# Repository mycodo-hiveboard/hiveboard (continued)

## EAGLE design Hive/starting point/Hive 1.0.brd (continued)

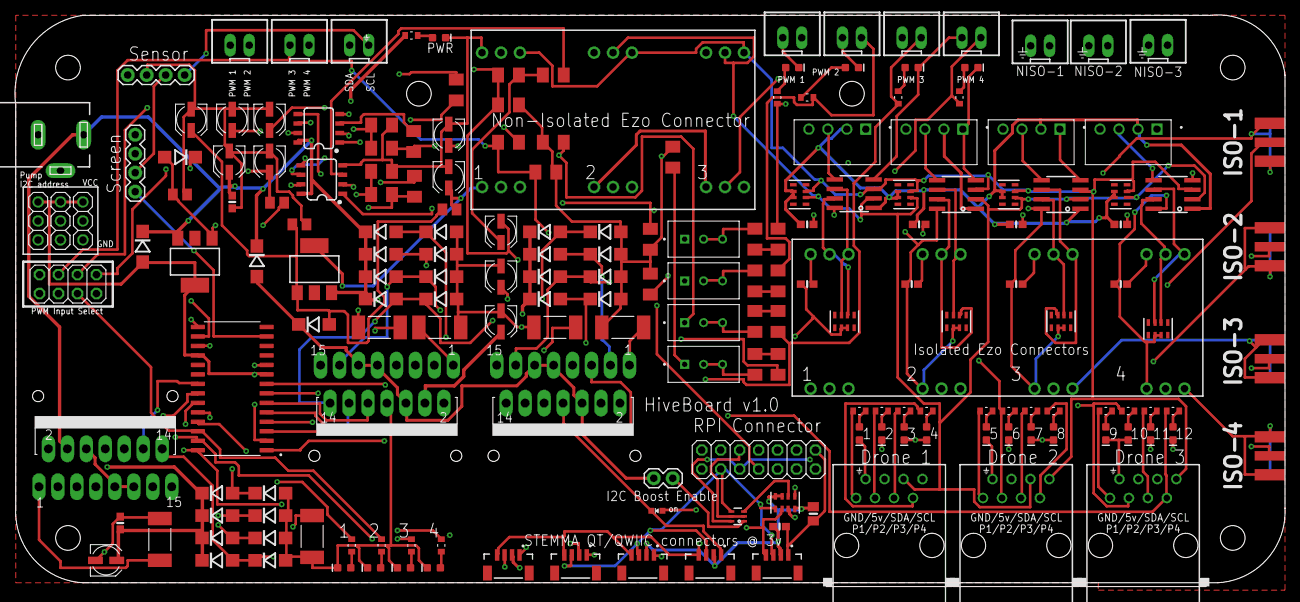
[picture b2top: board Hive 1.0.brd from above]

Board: 4 copper layers, 170.1 x 76.6 mm, 209 parts (0 on the bottom side), 127 nets.

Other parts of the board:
U$1, U$2: STAND-OFF

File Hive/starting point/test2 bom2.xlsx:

ID | Name | Designator | Footprint | Quantity | Manufacturer Part | Manufacturer | Supplier | Supplier Part | Price
1 | 100nF | C1,C2,C3 | C1206 | 3
2 | 1N4004 | D1,D10,D11,D12,D13,D14,D15,D16,D17,D18,D19,D2,D20,D21,D22,D23,D24,D3,D4,D5,D6,D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 | DO214BA | 26
3 | MOUNT-HOLE3.0 | H1,H2,H3,H4 | 3,0 | 4
4 | L298 | IC1,IC2,IC3 | MULTIWATT-15 | 3
5 | 0,5 x 2W | R1,R2,R3,R4,R5,R6 | R2512 | 6 | C469426
6 | RJ45-6L-B | PUMPBOX-1,PUMPBOX-3,PUMPBOX-2 | RJ45-NO-SHIELD | 3
7 | 1uf 50v | C1A1,C1B1,C1A2,C1B2 | C1206 | 4
8 | 100kΩ | R1A1,R1B1,R2A1,R2B1,R1A2,R1B2,R2A2,R2B2 | M1206 | 8
9 | 10kΩ | R5A1,R5B1,R5A2,R5B2 | M1206 | 4
10 | 75kΩ | R4A1,R4B1,R4A2,R4B2 | M1206 | 4
11 | 3296W-1-103 | R3-1A1,R3-1B1,R3-1A2,R3-1B2 | TRIM_3296W-1-103 | 4
12 | 180KΩ | R3-2A1,R3-2B1,R3-2A2,R3-2B2 | M1206 | 4
13 | 15kΩ | R3-3A1,R3-3B1,R3-3A2,R3-3B2 | M1206 | 4
14 | LM358 | U2,U1 | DIP08 | 2
15 | rr | X11 | JST-XH-02-PACKAGE-LONG-PAD | 1
16 | EZO2 | X12 | JST-XH-02-PACKAGE-LONG-PAD | 1
17 | PWM2 | (0-10V)-1 | JST-XH-02-PACKAGE-LONG-PAD | 1
18 | PWM1 | X4 | JST-XH-02-PACKAGE-LONG-PAD | 1
19 | PWM-IN | X5,X8 | JST-XH-02-PACKAGE-LONG-PAD | 2
20 | Sensor | X6 | JST-XH-04-PACKAGE-LONG-PAD | 1
21 | Screen Connector | X7 | JST-XH-04-PACKAGE-LONG-PAD | 1 | C225501
22 | 0.1uF | C6,C7,C4,C5,C8,C9,C10,C11,C15,C18 | 0603-NO | 10
23 | ISO154X | X13,X14,X16,X18 | SOIC8_150MIL | 4
24 | 10K | R9,R10,R7,R8,R11,R12,R13,R14 | RESPACK_4X0603 | 8
25 | RFM-0505S | PS1,PS2,PS3,PS4 | CONV_RFM-0505S | 4
26 | NISO-3 | X20 | JST-XH-02-PACKAGE-LONG-PAD | 1
27 | DATA | X21 | JST-XH-02-PACKAGE-LONG-PAD | 1
28 | 1X03-CLEANBIG | JP1,JP2,JP3,JP4,JP5,JP6,JP7,JP8,JP9,JP10,JP11,JP12,JP13,JP14 | 1X03-CLEANBIG | 14
29 | LM317MBSTT3 | IC4,IC5 | SOT223 | 2
30 | 240Ω | R15,R17 | M0805 | 2
31 | 1uF | C13,C16 | 085CS_1AR | 2 | C3348
32 | 10uF | C14,C17 | 085CS_1AR | 2 | C72485
33 | 394Ω | R16 | M0805 | 1
34 | 1X03 | SJ1,SJ2,SJ3 | 1X03 | 3
35 | 1N4002 | D33,D34 | DO214BA | 2
36 | 720Ω | R18 | M0805 | 1
37 | ISO-1 | ISO-1 | J502-ND-142-0701-801/806 | 1
38 | SMA-142-0701-801/806 | ISO-2,ISO-3,ISO-4 | J502-ND-142-0701-801/806 | 3
39 | CHIP-LED0603 | LED1,LED2,LED4,LED5,LED6,LED7,LED8,LED9,LED10,LED11,LED12,LED13,LED14,LED15,LED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 | CHIP-LED0603 | 25
40 | SDA | SDA | RESC1608X60N | 1
41 | 330R | SCL,12V,5V,3.3V,R20,R21,R22,R23,R24,R25,R26,R27,R28,R29,R30,R31,R32,R34,R33,R36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 | RESC1608X60N | 24
42 | MCP23017-E/SO | U3 | SOIC127P1030X265-28N | 1
43 | PWM4 | (0-10V)-2 | JST-XH-02-PACKAGE-LONG-PAD | 1
44 | PWM3 | X3 | JST-XH-02-PACKAGE-LONG-PAD | 1
45 | 2X04 | JP19 | 2X04 | 1
46 | 2X07 | JP15 | 2X07 | 1
47 | DCJ0202 | J1 | DCJ0202 | 1

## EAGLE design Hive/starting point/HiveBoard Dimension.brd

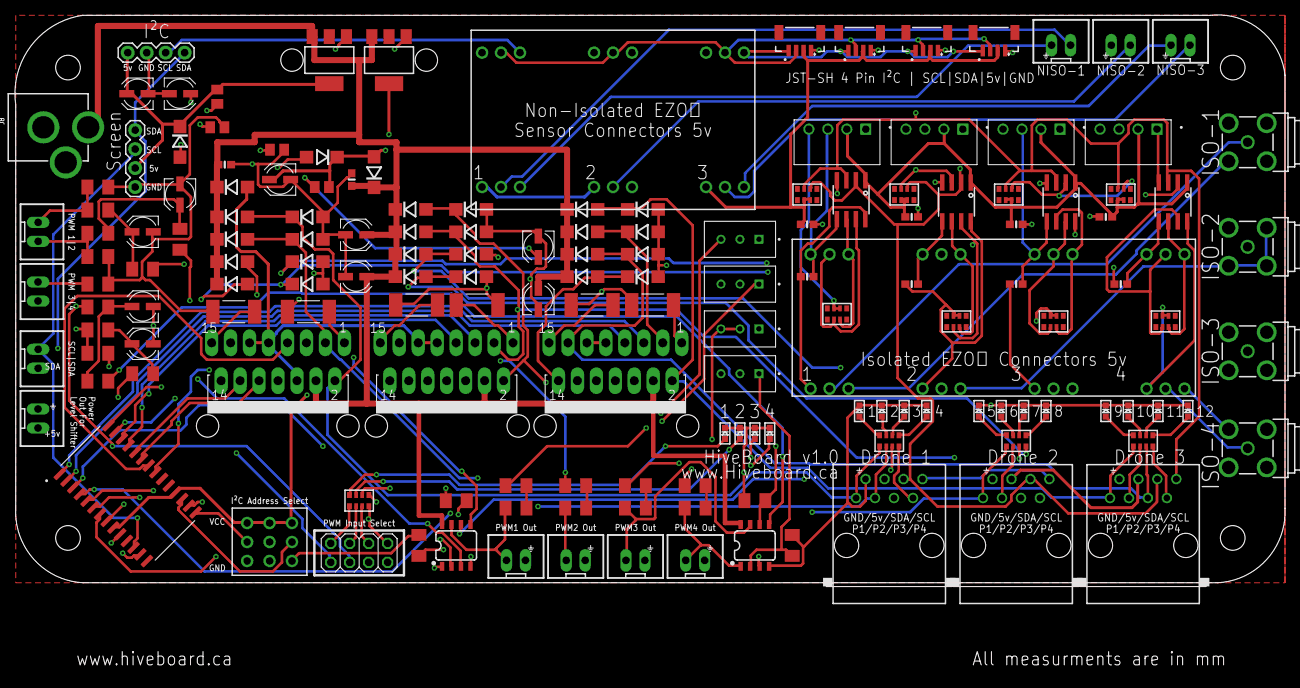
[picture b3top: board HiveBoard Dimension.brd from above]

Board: 4 copper layers, 170.1 x 76.6 mm, 178 parts (0 on the bottom side), 119 nets.

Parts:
C1, C7, C9: 100nF; UD-4X5,8_NICHICON
C1A1, C1A2, C1B1, C1B2, C5: 1uf 50v; UD-4X5,8_NICHICON
C2, C6, C10, C11, C12, C13, C14, C15, C16, C17: 0.1uF; 0603-NO
C3: 1uF 50v; UD-4X5,8_NICHICON
C4, C8: 10uF 35v; UD-4X5,8_NICHICON
D1, D2: 1N4002; DO214BA
D3, D4, D5, D6, D7, D8, D9, D10, D11, D12, D13, D14, D15, D16, D17, D18, D19, D20, D21, D22, D23, D24, D25, D26, D27, D28: 1N4004; DO214BA
H1, H2, H3, H4: STAND-OFF
IC1, IC3: LM317MBSTT3; SOT223
IC2, IC4, IC5: L298; MULTIWATT-15
J1, J5, J6, J7: Vertical Qwiic Connector; JST04_1MM_VERT
J2, J3: C2886705; 1X04
J8: POWER_JACK; POWER_JACK_PTH
JP1, JP2, JP3: 1X03_ROUND
JP4: 2X04
JP5, JP6, JP7, JP8, JP9, JP10, JP12, JP13, JP14, JP15, JP16, JP17, JP18, JP19: C2886705; 1X03-CLEANBIG
LED1, LED2, LED3, LED4, LED5, LED6, LED7, LED8, LED9, LED10, LED11, LED12, LED13, LED14, LED15, LED16: CHIPLED_0603
PS1, PS2, PS3, PS4: RFM-0505S; CONV_RFM-0505S
R1, R6, R8, R9, R10, R11: 0,5 x 2W; R2512
R1A1, R1A2, R1B1, R1B2, R2A1, R2A2, R2B1, R2B2: 100kΩ; M1206
R2, R3: 240Ω; M0805
R3-1A1, R3-1A2, R3-1B1, R3-1B2: 3296W-1-103; TRIM_3296W-1-103
R3-2A1, R3-2A2, R3-2B1, R3-2B2: 180KΩ; M1206
R3-3A1, R3-3A2, R3-3B1, R3-3B2: 15kΩ; M1206
R4: 720Ω; M0805
R4A1, R4A2, R4B1, R4B2: 75kΩ; M1206
R5: 394Ω; M0805
R5A1, R5A2, R5B1, R5B2: 10kΩ; M1206
R7, R15, R19, R22: 10kΩ; RESPACK_4X0603
R12, R13, R14, R16, R17, R18, R20, R21: 10KΩ; RESPACK_4X0603
U1: MCP23017-E/SO; SOIC127P1030X265-28N
U2, U3: LM358; SO08
X1, X2: PWM-IN; JST-XH-02-PACKAGE-LONG-PAD
X3, X11, X14, X17, X22: jst-xh-2; JST-XH-02-PACKAGE-LONG-PAD
X4: PWM1; JST-XH-02-PACKAGE-LONG-PAD
X5, X7: PWM2; JST-XH-02-PACKAGE-LONG-PAD
X6: PWM3; JST-XH-02-PACKAGE-LONG-PAD
X8, X10, X12, X15: ISO154X; SOIC8_150MIL
X9, X13, X16: RJ45-6L-B; RJ45-NO-SHIELD
X18, X19, X20, X21: BU-SMA-G

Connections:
+3.3V: C5.+, D11.C, D12.A, IC3.4, JP1.3, JP2.3, JP3.3, R3.2, U1.9, U1.18
+5V: C3.+, C10.1, C12.1, C14.1, C16.1, D1.C, D2.A, IC1.4, IC2.6, IC2.9, IC2.11, IC4.6, IC4.9, IC4.11, IC5.6, IC5.9, IC5.11, J1.3, J2.1, J3.2, J5.3, J6.3, J7.3, JP6.1, JP8.1, JP10.1, PS1.2, PS2.2, PS3.2, PS4.2, R2.2, R12.6, R12.7, R13.6, R13.7, R17.6, R17.7, R20.6, R20.7, X8.1, X9.4, X10.1, X12.1, X13.4, X15.1, X16.4, X22.2
+12V: C1.+, C2.2, C6.2, C7.+, C9.+, D2.C, D3.C, D5.C, D7.C, D9.C, D12.C, D13.C, D14.C, D15.C, D16.C, D21.C, D23.C, D25.C, D27.C, IC1.3, IC2.4, IC3.3, IC4.4, IC5.4, J8.PWR, U2.8, U3.8
GND: C1.-, C1A1.-, C1A2.-, C1B1.-, C1B2.-, C2.1, C3.-, C4.-, C5.-, C6.1, C7.-, C8.-, C9.-, C10.2, C12.2, C14.2, C16.2, D4.A, D6.A, D8.A, D10.A, D17.A, D18.A, D19.A, D20.A, D22.A, D24.A, D26.A, D28.A, IC2.8, IC4.8, IC5.8, J1.4, J2.2, J3.1, J5.4, J6.4, J7.4, J8.GND, J8.GNDBREAK, JP1.1, JP2.1, JP3.1, JP5.3, JP7.3, JP9.3, LED1.C, LED2.C, LED3.C, LED4.C, LED5.C, LED6.C, LED7.C, LED8.C, LED9.C, LED10.C, LED11.C, LED12.C, LED13.C, LED14.C, LED15.C, LED16.C, PS1.1, PS2.1, PS3.1, PS4.1, R1.1, R2A1.1, R2A2.1, R2B1.2, R2B2.2, R4.1, R5.1, R5A1.2, R5A2.2, R5B1.2, R5B2.2, R6.1, R8.1, R9.1, R10.1, R11.1, U1.10, U2.4, U3.4, X4.2, X5.2, X6.2, X7.2, X8.4, X9.2, X10.4, X12.4, X13.2, X15.4, X16.2, X22.1
IN-PUMP-1: IC2.5, U1.21
IN-PUMP-2: IC2.7, U1.22
IN-PUMP-3: IC2.10, U1.23
IN-PUMP-4: IC2.12, U1.24
IN-PUMP-5: IC4.5, U1.25
IN-PUMP-6: IC4.7, U1.26
IN-PUMP-7: IC4.10, U1.27
IN-PUMP-8: IC4.12, U1.28
IN-PUMP-9: IC5.5, U1.1
IN-PUMP-10: IC5.7, U1.2
IN-PUMP-11: IC5.10, U1.3
IN-PUMP-12: IC5.12, U1.4
IN-PWM-1: JP4.7, R1A1.2, R5A1.1, X1.1
IN-PWM-2: JP4.5, R1B1.1, R5B1.1, X1.2
IN-PWM-3: JP4.3, R1A2.2, R5A2.1, X2.1
IN-PWM-4: JP4.1, R1B2.1, R5B2.1, X2.2
ISO-1-5V: C11.1, JP13.1, PS1.4, R14.6, R14.7, X8.8
ISO-2-5V: C13.1, JP15.1, PS2.4, R16.6, R16.7, X10.8
ISO-3-5V: C15.1, JP17.1, PS3.4, R18.6, R18.7, X12.8
ISO-4-5V: C17.1, JP19.1, PS4.4, R21.6, R21.7, X15.8
ISO-GND-1: C11.2, JP12.3, PS1.3, X8.5
ISO-GND-2: C13.2, JP14.3, PS2.3, X10.5
ISO-GND-3: C15.2, JP16.3, PS3.3, X12.5
ISO-GND-4: C17.2, JP18.3, PS4.3, X15.5
ISO-PRB-1+: JP13.2, X18.1
ISO-PRB-1GND: JP13.3, X18.2, X18.3, X18.4, X18.5
ISO-PRB-2+: JP15.2, X19.1
ISO-PRB-2GND: JP15.3, X19.2, X19.3, X19.4, X19.5
ISO-PRB-3+: JP17.2, X20.1
ISO-PRB-3GND: JP17.3, X20.2, X20.3, X20.4, X20.5
ISO-PRB-4+: JP19.2, X21.1
ISO-PRB-4GND: JP19.3, X21.2, X21.3, X21.4, X21.5
LED1: JP4.2, R7.1, U1.5
LED2: JP4.4, R7.2, U1.6
LED3: JP4.6, R7.3, U1.7
LED4: JP4.8, R7.4, U1.8
unnamed: IC4.1, R9.2
unnamed: IC4.15, R8.2
unnamed: IC5.1, R11.2
unnamed: IC5.15, R10.2
unnamed: C8.+, D11.A, IC3.1, R3.1, R5.2
unnamed: R2A1.2, R3-1A1.1, U2.6
unnamed: LED1.A, R7.8
unnamed: R2B1.1, R3-1B1.1, U2.2
unnamed: IC2.1, R1.2
unnamed: IC2.15, R6.2
unnamed: C4.+, D1.A, IC1.1, R2.1, R4.2
unnamed: LED2.A, R7.7
unnamed: R3-1B1.2, R3-1B1.3, R3-2B1.1
unnamed: R3-2B1.2, R3-3B1.1
unnamed: R3-1A1.2, R3-1A1.3, R3-2A1.1
unnamed: R3-2A1.2, R3-3A1.1
unnamed: C1A1.+, R1A1.1, R4A2.1
unnamed: C1B1.+, R1B1.2, R4B1.1
unnamed: LED13.A, R22.8
unnamed: LED14.A, R22.7
unnamed: R4A2.2, U2.5
unnamed: R4B1.2, U2.3
unnamed: R3-1B2.2, R3-1B2.3, R3-2B2.1
unnamed: LED15.A, R22.6
unnamed: LED16.A, R22.5
unnamed: LED8.A, R15.5
unnamed: LED7.A, R15.6
unnamed: LED6.A, R15.7
unnamed: LED5.A, R15.8
unnamed: LED9.A, R19.8
unnamed: LED10.A, R19.7
unnamed: LED11.A, R19.6
unnamed: LED12.A, R19.5
unnamed: LED3.A, R7.6
unnamed: LED4.A, R7.5
unnamed: R3-2B2.2, R3-3B2.1
unnamed: R3-1A2.2, R3-1A2.3, R3-2A2.1
unnamed: R3-2A2.2, R3-3A2.1
unnamed: C1A2.+, R1A2.1, R4A1.1
unnamed: C1B2.+, R1B2.2, R4B2.1
unnamed: R2A2.2, R3-1A2.1, U3.6
unnamed: R2B2.1, R3-1B2.1, U3.2
unnamed: R4A1.2, U3.5
unnamed: R4B2.2, U3.3
unnamed: JP1.2, U1.15
unnamed: JP2.2, U1.16
unnamed: JP3.2, U1.17
NISO-PRB-1+: JP6.2, X11.2
NISO-PRB-1GND: JP6.3, X11.1
NISO-PRB-2+: JP8.2, X14.2
NISO-PRB-2GND: JP8.3, X14.1
NISO-PRB-3+: JP10.2, X17.2
NISO-PRB-3GND: JP10.3, X17.1
OUT-PUMP-1: D3.A, D4.C, IC2.2, R15.1, X9.1
OUT-PUMP-2: D5.A, D6.C, IC2.3, R15.2, X9.3
OUT-PUMP-3: D7.A, D8.C, IC2.13, R15.3, X9.5
OUT-PUMP-4: D9.A, D10.C, IC2.14, R15.4, X9.7
OUT-PUMP-5: D13.A, D17.C, IC4.2, R19.1, X13.1
OUT-PUMP-6: D14.A, D18.C, IC4.3, R19.2, X13.3
OUT-PUMP-7: D15.A, D19.C, IC4.13, R19.3, X13.5
OUT-PUMP-8: D16.A, D20.C, IC4.14, R19.4, X13.7
OUT-PUMP-9: D21.A, D22.C, IC5.2, R22.1, X16.1
OUT-PUMP-10: D23.A, D24.C, IC5.3, R22.2, X16.3
OUT-PUMP-11: D25.A, D26.C, IC5.13, R22.3, X16.5
OUT-PUMP-12: D27.A, D28.C, IC5.14, R22.4, X16.7
PWM-OUT-1: R3-3A1.2, U2.7, X4.1
PWM-OUT-2: R3-3B1.2, U2.1, X5.1
PWM-OUT-3: R3-3A2.2, U3.7, X6.1
PWM-OUT-4: R3-3B2.2, U3.1, X7.1
SCL: J1.1, J2.3, J3.3, J5.1, J6.1, J7.1, JP5.1, JP7.1, JP9.1, R12.3, R13.3, R17.3, R20.3, U1.12, X3.1, X8.3, X9.8, X10.3, X12.3, X13.8, X15.3, X16.8
SCL2: JP12.1, R14.3, X8.6
SCL3: JP14.1, R16.3, X10.6
SCL4: JP16.1, R18.3, X12.6
SCL5: JP18.1, R21.3, X15.6
SDA: J1.2, J2.4, J3.4, J5.2, J6.2, J7.2, JP5.2, JP7.2, JP9.2, R12.2, R13.2, R17.2, R20.2, U1.13, X3.2, X8.2, X9.6, X10.2, X12.2, X13.6, X15.2, X16.6
SDA2: JP12.2, R14.2, X8.7
SDA3: JP14.2, R16.2, X10.7
SDA4: JP16.2, R18.2, X12.7
SDA5: JP18.2, R21.2, X15.7

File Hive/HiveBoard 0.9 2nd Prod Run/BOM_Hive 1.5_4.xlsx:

No. | Quantity | Comment | Designator | Footprint | Value | Manufacturer Part | Manufacturer | Supplier Part | Supplier
1 | 3 | 100nF | C1,C7,C9 | UD-4X5,8_NICHICON | C271438
2 | 5 | 1uf 50v | C1A1,C1A2,C1B1,C1B2,C5 | UD-4X5,8_NICHICON | C3348
3 | 10 | 0.1uF | C2,C6,C10,C11,C12,C13,C14,C15,C16,C17 | 0603-NO
4 | 1 | 1uF 50v | C3 | UD-4X5,8_NICHICON | C3348
5 | 2 | 10uF 35v | C4,C8 | UD-4X5,8_NICHICON | C72485
6 | 2 | 1N4002 | D1,D2 | DO214BA
7 | 26 | 1N4004 | D3,D4,D5,D6,D7,D8,D9,D10,D11,D12,D13,D14,D15,D16,D17,D18,D19,D20,D21,D22,D23,D2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 | DO214BA
8 | 4 | STAND-OFF | H1,H2,H3,H4 | STAND-OFF
9 | 2 | LM317MBSTT3 | IC1,IC3 | SOT223
10 | 3 | L298 | IC2,IC4,IC5 | MULTIWATT-15
11 | 2 | C2886705 | J2,J3 | 1X04 | C2718488
12 | 4 | Vertical Qwiic Connector | J4,J5,J6,J7 | JST04_1MM_VERT | C2859067
13 | 1 | POWER_JACK | J8 | POWER_JACK_PTH | C16214
14 | 3 |  | JP1,JP2,JP3 | 1X03_ROUND | C49257
15 | 1 |  | JP4 | 2X04 | C124386
16 | 14 | C2886705 | JP5,JP6,JP7,JP8,JP9,JP10,JP12,JP13,JP14,JP15,JP16,JP17,JP18,JP19 | 1X03-CLEANBIG | C2932670
17 | 1 |  | JP11 | 2X07 | C71397
18 | 16 |  | LED1,LED2,LED3,LED4,LED5,LED6,LED7,LED8,LED9,LED10,LED11,LED12,LED13,LED14,LED1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 | CHIPLED_0603 | C84266
19 | 4 | RFM-0505S | PS1,PS2,PS3,PS4 | CONV_RFM-0505S
20 | 6 | 0,5 x 2W | R1,R6,R8,R9,R10,R11 | R2512 | C469426
21 | 8 | 100kΩ | R1A1,R1A2,R1B1,R1B2,R2A1,R2A2,R2B1,R2B2 | M1206
22 | 2 | 240Ω | R2,R3 | M0805
23 | 4 | 3296W-1-103 | R3-1A1,R3-1A2,R3-1B1,R3-1B2 | TRIM_3296W-1-103
24 | 4 | 180KΩ | R3-2A1,R3-2A2,R3-2B1,R3-2B2 | M1206
25 | 4 | 15kΩ | R3-3A1,R3-3A2,R3-3B1,R3-3B2 | M1206
26 | 1 | 720Ω | R4 | M0805 | c17813
27 | 4 | 75kΩ | R4A1,R4A2,R4B1,R4B2 | M1206 | C17986
28 | 1 | 394Ω | R5 | M0805
29 | 4 | 10kΩ | R5A1,R5A2,R5B1,R5B2 | M1206
30 | 4 | 10kΩ | R7,R15,R19,R22 | RESPACK_4X0603 | C29718
31 | 8 | 10KΩ | R12,R13,R14,R16,R17,R18,R20,R21 | RESPACK_4X0603 | C29718
32 | 1 | MCP23017-E/SO | U1 | SOIC127P1030X265-28N | C629440
33 | 2 | LM358 | U2,U3 | SO08
34 | 2 |  | U$1,U$4 | STAND-OFF
35 | 1 |  | U$2 | QWIIC_6MM
36 | 2 | PWM-IN | X1,X2 | JST-XH-02-PACKAGE-LONG-PAD
37 | 4 | jst-xh-2 | X3,X11,X14,X17 | JST-XH-02-PACKAGE-LONG-PAD
38 | 1 | PWM1 | X4 | JST-XH-02-PACKAGE-LONG-PAD
39 | 2 | PWM2 | X5,X7 | JST-XH-02-PACKAGE-LONG-PAD
40 | 1 | PWM3 | X6 | JST-XH-02-PACKAGE-LONG-PAD
41 | 4 | ISO154X | X8,X10,X12,X15 | SOIC8_150MIL
42 | 3 | RJ45-6L-B | X9,X13,X16 | RJ45-NO-SHIELD
43 | 4 | BU-SMA-G | X18,X19,X20,X21 | BU-SMA-G | C914553

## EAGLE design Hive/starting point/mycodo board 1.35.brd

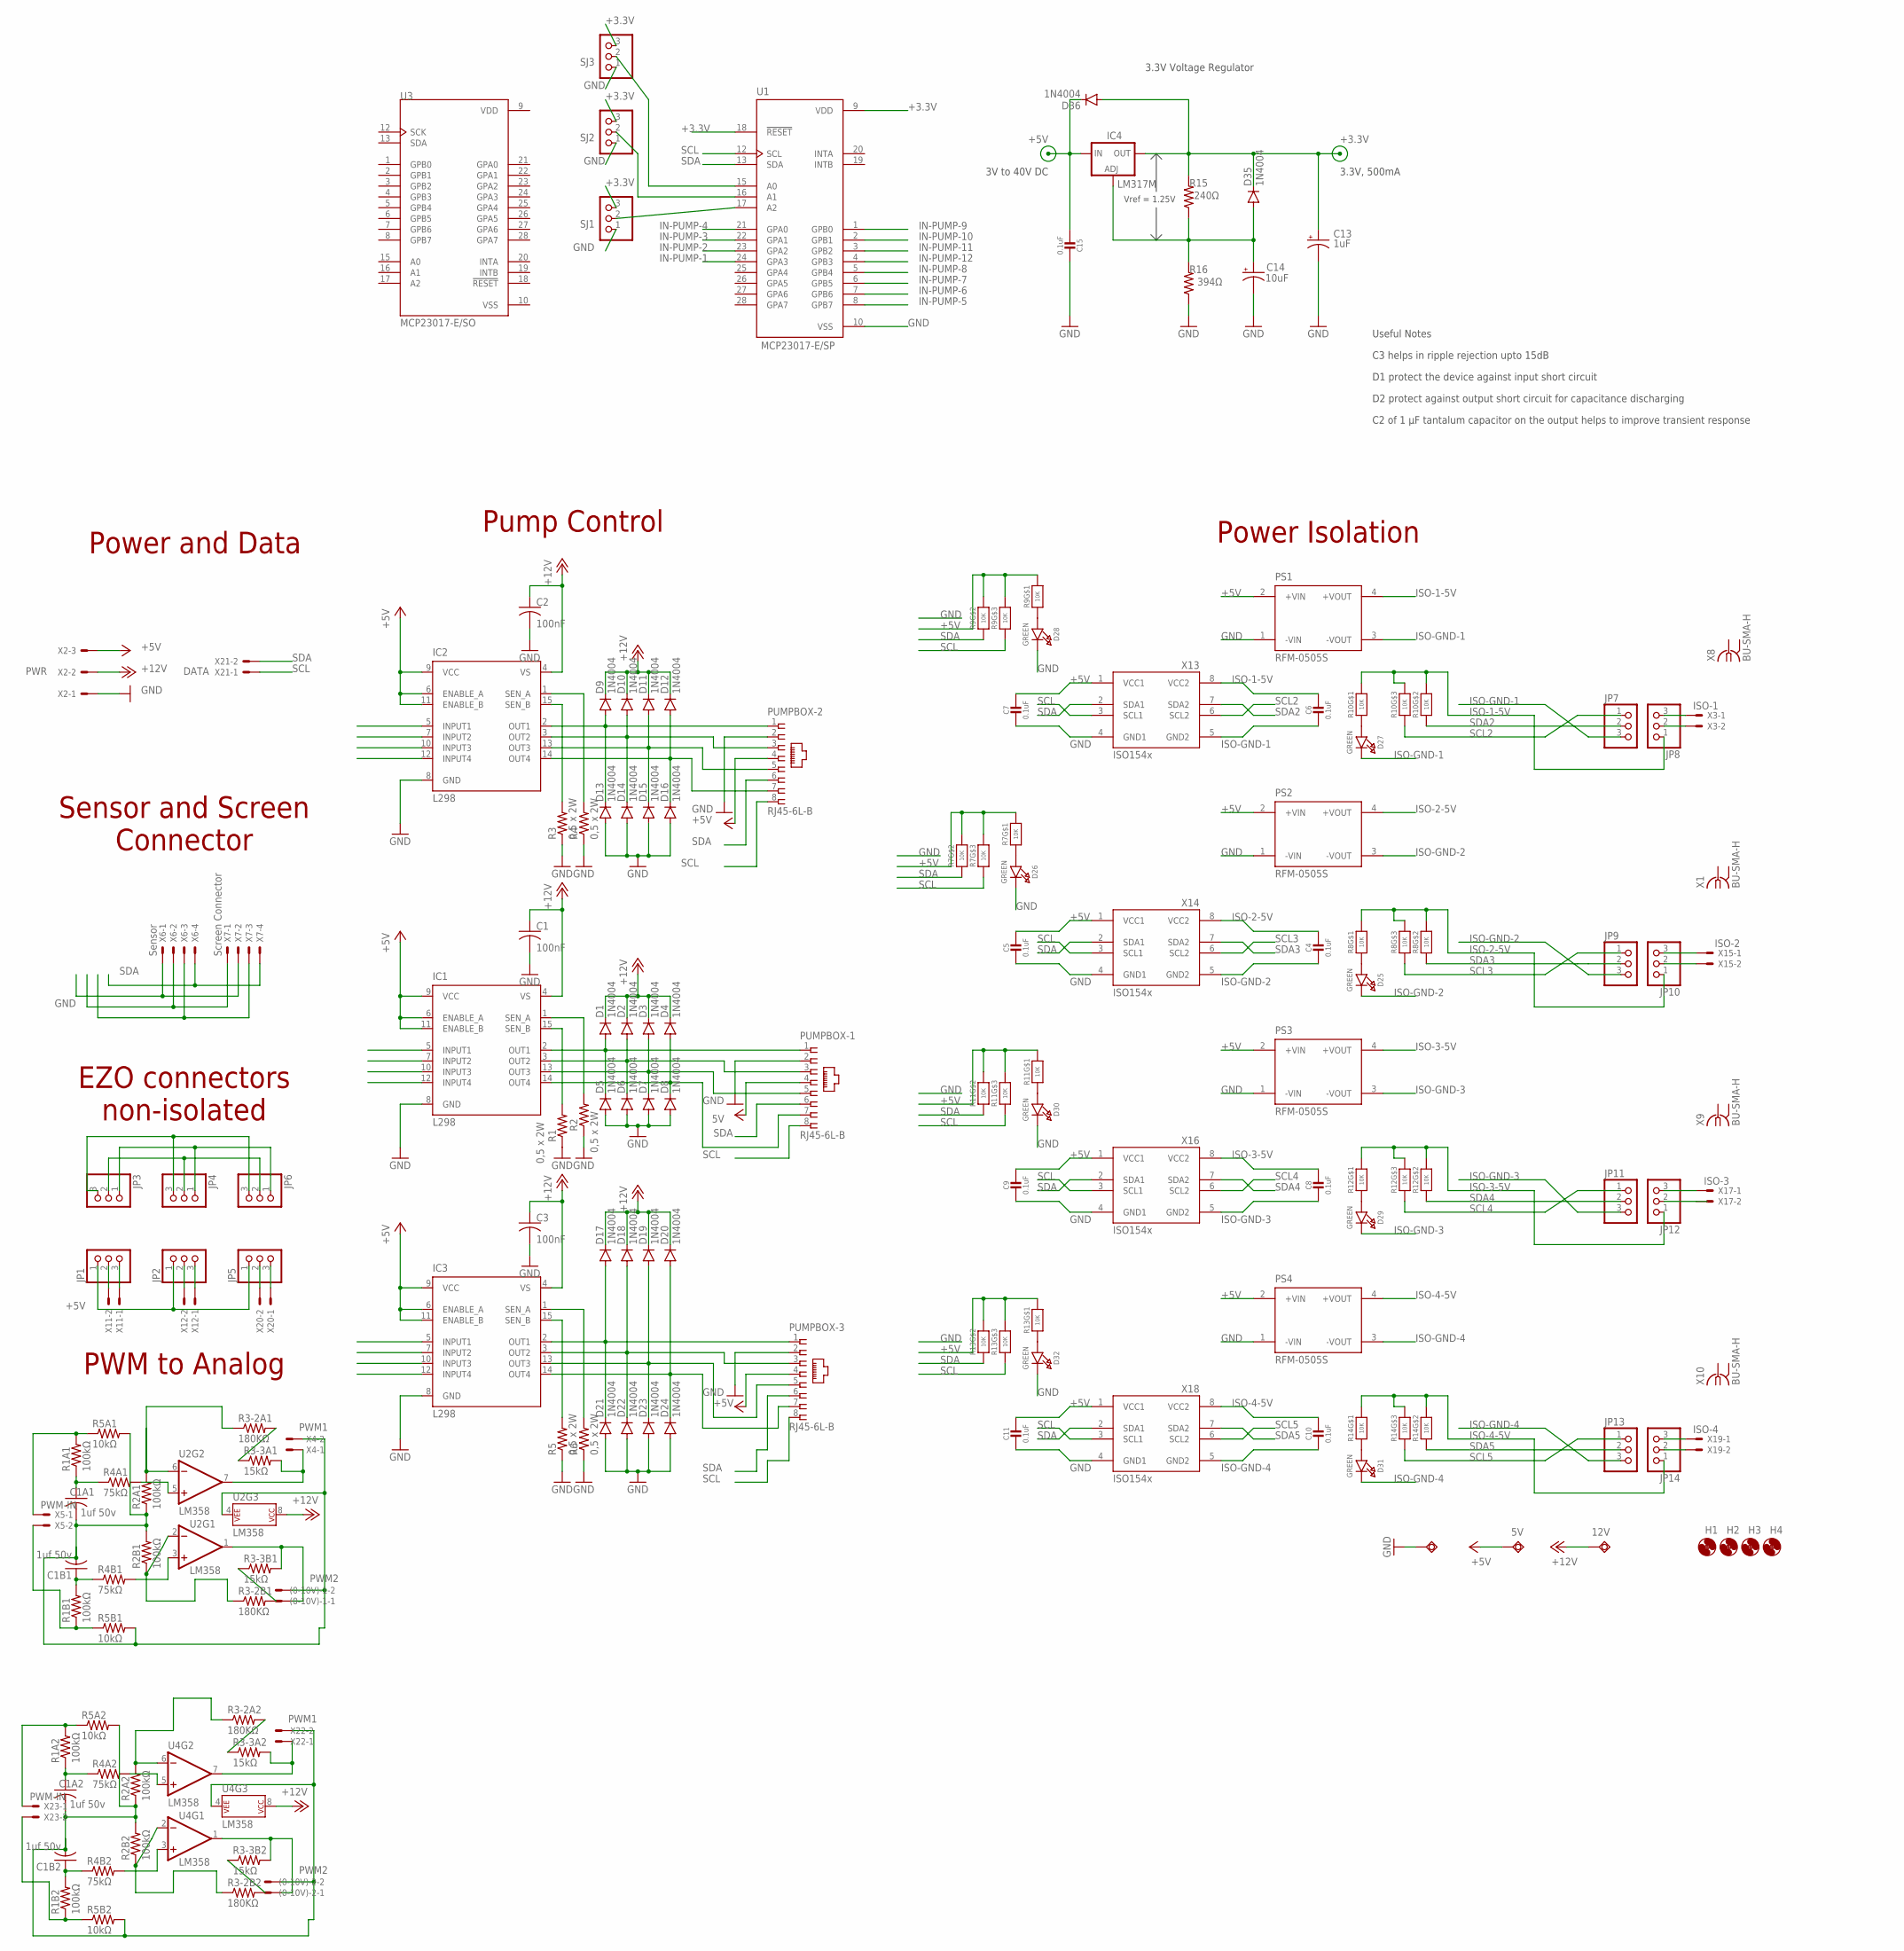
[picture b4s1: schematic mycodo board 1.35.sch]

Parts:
5V, 12V: TPSQTP20SQ; TP20SQ
(0-10V)-1, (0-10V)-2: PWM2; JST-XH-02-PACKAGE-LONG-PAD
C1, C2, C3: 100nF; C1206
C1A1, C1A2, C1B1, C1B2: 1uf 50v; C1206
C4, C5, C6, C7, C8, C9, C10, C11, C15: 0.1uF; 0603-NO
C13: 1uF; 085CS_1AR
C14: 10uF; 085CS_1AR
D1, D2, D3, D4, D5, D6, D7, D8, D9, D10, D11, D12, D13, D14, D15, D16, D17, D18, D19, D20, D21, D22, D23, D24, D35, D36: 1N4004; DO214BA
D25, D26, D27, D28, D29, D30, D31, D32: GREEN; CHIPLED_0603_NOOUTLINE
GND: TPSQTP20SQ; TP20SQ
H1, H2, H3, H4: MOUNT-HOLE3.0; 3,0
IC1, IC2, IC3: L298; MULTIWATT-15
IC4: LM317MBSTT3; SOT223; PARTNUMBER LM317M
JP1, JP2, JP3, JP4, JP5, JP6, JP7, JP8, JP9, JP10, JP11, JP12, JP13, JP14: PINHD-1X3CB; 1X03-CLEANBIG
PS1, PS2, PS3, PS4: RFM-0505S; CONV_RFM-0505S
PUMPBOX-1, PUMPBOX-2, PUMPBOX-3: RJ45-6L-B; RJ45-NO-SHIELD
R1, R2, R3, R4, R5, R6: 0,5 x 2W; R2512
R1A1, R1A2, R1B1, R1B2, R2A1, R2A2, R2B1, R2B2: 100kΩ; M1206
R3-2A1, R3-2A2, R3-2B1, R3-2B2: 180KΩ; M1206
R3-3A1, R3-3A2, R3-3B1, R3-3B2: 15kΩ; M1206
R4A1, R4A2, R4B1, R4B2: 75kΩ; M1206
R5A1, R5A2, R5B1, R5B2: 10kΩ; M1206
R7, R8, R9, R10, R11, R12, R13, R14: 10K; RESPACK_4X0603
R15: 240Ω; M0805
R16: 394Ω; M0805
SJ1, SJ2, SJ3: PINHD-1X3; 1X03
U1: MCP23017-E/SP; DIP787W45P254L3556H508Q28
U2, U4: LM358; DIP08
U3: MCP23017-E/SO; SOIC127P1030X265-28N
X1, X8, X9, X10: BU-SMA-H
X2: PWR; JST-XH-03-PACKAGE-LONG-PAD
X3: ISO-1; JST-XH-02-PACKAGE-LONG-PAD
X4, X22: PWM1; JST-XH-02-PACKAGE-LONG-PAD
X5, X23: PWM-IN; JST-XH-02-PACKAGE-LONG-PAD
X6: Sensor; JST-XH-04-PACKAGE-LONG-PAD
X7: Screen Connector; JST-XH-04-PACKAGE-LONG-PAD
X11: rr; JST-XH-02-PACKAGE-LONG-PAD
X12: EZO2; JST-XH-02-PACKAGE-LONG-PAD
X13, X14, X16, X18: ISO154X; SOIC8_150MIL
X15: ISO-2; JST-XH-02-PACKAGE-LONG-PAD
X17: ISO-3; JST-XH-02-PACKAGE-LONG-PAD
X19: ISO-4; JST-XH-02-PACKAGE-LONG-PAD
X20: NISO-3; JST-XH-02-PACKAGE-LONG-PAD
X21: DATA; JST-XH-02-PACKAGE-LONG-PAD

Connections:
+3.3V: C13.+, D35.C, D36.A, IC4.4 (OUT), R15.2, SJ1.3, SJ2.3, SJ3.3, U1.9 (VDD), U1.18 (!RESET)
+5V: 5V.TP, C5.1, C7.1, C9.1, C11.1, C15.2, D36.C, IC1.6 (ENABLE_A), IC1.9 (VCC), IC1.11 (ENABLE_B), IC2.6 (ENABLE_A), IC2.9 (VCC), IC2.11 (ENABLE_B), IC3.6 (ENABLE_A), IC3.9 (VCC), IC3.11 (ENABLE_B), IC4.3 (IN), JP1.1, JP2.1, JP5.1, PS1.2 (+VIN), PS2.2 (+VIN), PS3.2 (+VIN), PS4.2 (+VIN), PUMPBOX-1.4, PUMPBOX-2.4, PUMPBOX-3.4, R7.6 (2), R7.7 (2), R7.8 (2), R9.6 (2), R9.7 (2), R9.8 (2), R11.6 (2), R11.7 (2), R11.8 (2), R13.6 (2), R13.7 (2), R13.8 (2), X2.3, X6.1, X7.2, X13.1 (VCC1), X14.1 (VCC1), X16.1 (VCC1), X18.1 (VCC1)
+12V: 12V.TP, C1.1, C2.1, C3.1, D1.C, D2.C, D3.C, D4.C, D9.C, D10.C, D11.C, D12.C, D17.C, D18.C, D19.C, D20.C, IC1.4 (VS), IC2.4 (VS), IC3.4 (VS), U2.8 (P$V+), U4.8 (P$V+), X2.2
GND: (0-10V)-1.2, C1.2, C1A1.2, C1B1.2, C2.2, C3.2, C5.2, C7.2, C9.2, C11.2, C13.-, C14.-, C15.1, D5.A, D6.A, D7.A, D8.A, D13.A, D14.A, D15.A, D16.A, D21.A, D22.A, D23.A, D24.A, D26.C, D28.C, D30.C, D32.C, GND.TP, IC1.8 (GND), IC2.8 (GND), IC3.8 (GND), JP3.3, JP4.3, JP6.3, PS1.1 (-VIN), PS2.1 (-VIN), PS3.1 (-VIN), PS4.1 (-VIN), PUMPBOX-1.2, PUMPBOX-2.2, PUMPBOX-3.2, R1.1, R2.1, R2A1.1, R2B1.2, R3.1, R4.1, R5.1, R5A1.2, R5B1.2, R6.1, R16.1, SJ1.1, SJ2.1, SJ3.1, U1.10 (VSS), U2.4 (P$V-), X2.1, X4.2, X6.2, X7.1, X13.4 (GND1), X14.4 (GND1), X16.4 (GND1), X18.4 (GND1)
GND1: (0-10V)-2.2, C1A2.2, C1B2.2, R2A2.1, R2B2.2, R5A2.2, R5B2.2, U4.4 (P$V-), X22.2
IN-PUMP-1: IC1.5 (INPUT1), U1.24 (GPA3)
IN-PUMP-2: IC1.7 (INPUT2), U1.23 (GPA2)
IN-PUMP-3: IC1.10 (INPUT3), U1.22 (GPA1)
IN-PUMP-4: IC1.12 (INPUT4), U1.21 (GPA0)
IN-PUMP-5: IC2.5 (INPUT1), U1.8 (GPB7)
IN-PUMP-6: IC2.7 (INPUT2), U1.7 (GPB6)
IN-PUMP-7: IC2.10 (INPUT3), U1.6 (GPB5)
IN-PUMP-8: IC2.12 (INPUT4), U1.5 (GPB4)
IN-PUMP-9: IC3.5 (INPUT1), U1.1 (GPB0)
IN-PUMP-10: IC3.7 (INPUT2), U1.2 (GPB1)
IN-PUMP-11: IC3.10 (INPUT3), U1.3 (GPB2)
IN-PUMP-12: IC3.12 (INPUT4), U1.4 (GPB3)
IN-PWM-1: R1A1.2, R5A1.1, X5.1
IN-PWM-2: R1B1.1, R5B1.1, X5.2
IN-PWM-3: R1A2.2, R5A2.1, X23.1
IN-PWM-4: R1B2.1, R5B2.1, X23.2
ISO-1-5V: C6.1, JP8.1, PS1.4 (+VOUT), R10.6 (2), R10.7 (2), R10.8 (2), X13.8 (VCC2)
ISO-2-5V: C4.1, JP10.1, PS2.4 (+VOUT), R8.6 (2), R8.7 (2), R8.8 (2), X14.8 (VCC2)
ISO-3-5V: C8.1, JP12.1, PS3.4 (+VOUT), R12.6 (2), R12.7 (2), R12.8 (2), X16.8 (VCC2)
ISO-4-5V: C10.1, JP14.1, PS4.4 (+VOUT), R14.6 (2), R14.7 (2), R14.8 (2), X18.8 (VCC2)
ISO-GND-1: C6.2, D27.C, JP7.3, PS1.3 (-VOUT), X13.5 (GND2)
ISO-GND-2: C4.2, D25.C, JP9.3, PS2.3 (-VOUT), X14.5 (GND2)
ISO-GND-3: C8.2, D29.C, JP11.3, PS3.3 (-VOUT), X16.5 (GND2)
ISO-GND-4: C10.2, D31.C, JP13.3, PS4.3 (-VOUT), X18.5 (GND2)
unnamed: IC2.1 (SEN_A), R4.2
unnamed: IC2.15 (SEN_B), R3.2
unnamed: IC3.1 (SEN_A), R6.2
unnamed: IC3.15 (SEN_B), R5.2
unnamed: C14.+, D35.A, IC4.1 (ADJ), R15.1, R16.2
unnamed: SJ1.2, U1.17 (A2)
unnamed: SJ2.2, U1.16 (A1)
unnamed: SJ3.2, U1.15 (A0)
unnamed: IC1.1 (SEN_A), R2.2
unnamed: IC1.15 (SEN_B), R1.2
unnamed: R2B2.1, R3-2B2.1, U4.2 (-IN)
unnamed: R3-2B2.2, R3-3B2.1
unnamed: R2A2.2, R3-2A2.1, U4.6 (-IN)
unnamed: R3-2A2.2, R3-3A2.1
unnamed: JP8.3, X3.1
unnamed: JP8.2, X3.2
unnamed: R3-2B1.2, R3-3B1.1
unnamed: R2A1.2, R3-2A1.1, U2.6 (-IN)
unnamed: R3-2A1.2, R3-3A1.1
unnamed: C1A1.1, R1A1.1, R4A1.1
unnamed: C1B1.1, R1B1.2, R4B1.1
unnamed: R2B1.1, R3-2B1.1, U2.2 (-IN)
unnamed: R4A1.2, U2.5 (+IN)
unnamed: R4B1.2, U2.3 (+IN)
unnamed: D28.A, R9.1
unnamed: D27.A, R10.1
unnamed: D26.A, R7.1
unnamed: D25.A, R8.1
unnamed: JP10.3, X15.1
unnamed: JP10.2, X15.2
unnamed: D30.A, R11.1
unnamed: D29.A, R12.1
unnamed: JP12.3, X17.1
unnamed: JP12.2, X17.2
unnamed: D32.A, R13.1
unnamed: D31.A, R14.1
unnamed: JP14.3, X19.1
unnamed: JP14.2, X19.2
unnamed: JP5.3, X20.1
unnamed: JP5.2, X20.2
unnamed: JP2.2, X12.2
unnamed: JP2.3, X12.1
unnamed: JP1.2, X11.2
unnamed: JP1.3, X11.1
unnamed: C1A2.1, R1A2.1, R4A2.1
unnamed: C1B2.1, R1B2.2, R4B2.1
unnamed: R4A2.2, U4.5 (+IN)
unnamed: R4B2.2, U4.3 (+IN)
OUT-PUMP-1: D1.A, D5.C, IC1.2 (OUT1), PUMPBOX-1.1
OUT-PUMP-2: D2.A, D6.C, IC1.3 (OUT2), PUMPBOX-1.3
OUT-PUMP-3: D3.A, D7.C, IC1.13 (OUT3), PUMPBOX-1.5
OUT-PUMP-4: D4.A, D8.C, IC1.14 (OUT4), PUMPBOX-1.7
OUT-PUMP-5: D9.A, D13.C, IC2.2 (OUT1), PUMPBOX-2.1
OUT-PUMP-6: D10.A, D14.C, IC2.3 (OUT2), PUMPBOX-2.3
OUT-PUMP-7: D11.A, D15.C, IC2.13 (OUT3), PUMPBOX-2.5
OUT-PUMP-8: D12.A, D16.C, IC2.14 (OUT4), PUMPBOX-2.7
OUT-PUMP-9: D17.A, D21.C, IC3.2 (OUT1), PUMPBOX-3.1
OUT-PUMP-10: D18.A, D22.C, IC3.3 (OUT2), PUMPBOX-3.3
OUT-PUMP-11: D19.A, D23.C, IC3.13 (OUT3), PUMPBOX-3.5
OUT-PUMP-12: D20.A, D24.C, IC3.14 (OUT4), PUMPBOX-3.7
OUTA: R3-3A1.2, U2.7 (OUT), X4.1
OUTA1: R3-3A2.2, U4.7 (OUT), X22.1
OUTB: (0-10V)-1.1, R3-3B1.2, U2.1 (OUT)
OUTB1: (0-10V)-2.1, R3-3B2.2, U4.1 (OUT)
SCL: JP3.1, JP4.1, JP6.1, PUMPBOX-1.8, PUMPBOX-2.8, PUMPBOX-3.8, R7.3 (1), R9.3 (1), R11.3 (1), R13.3 (1), U1.12 (SCL), X6.3, X7.3, X13.3 (SCL1), X14.3 (SCL1), X16.3 (SCL1), X18.3 (SCL1), X21.1
SCL2: JP7.1, R10.3 (1), X13.6 (SCL2)
SCL3: JP9.1, R8.3 (1), X14.6 (SCL2)
SCL4: JP11.1, R12.3 (1), X16.6 (SCL2)
SCL5: JP13.1, R14.3 (1), X18.6 (SCL2)
SDA: JP3.2, JP4.2, JP6.2, PUMPBOX-1.6, PUMPBOX-2.6, PUMPBOX-3.6, R7.2 (1), R9.2 (1), R11.2 (1), R13.2 (1), U1.13 (SDA), X6.4, X7.4, X13.2 (SDA1), X14.2 (SDA1), X16.2 (SDA1), X18.2 (SDA1), X21.2
SDA2: JP7.2, R10.2 (1), X13.7 (SDA2)
SDA3: JP9.2, R8.2 (1), X14.7 (SDA2)
SDA4: JP11.2, R12.2 (1), X16.7 (SDA2)
SDA5: JP13.2, R14.2 (1), X18.7 (SDA2)
VDD: U3.9 (VDD)
VSS: U3.10 (VSS)

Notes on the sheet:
Power Isolation
Pump Control
PWM to Analog
EZO connectors non-isolated
Sensor and Screen Connector
Power and Data
3.3V Voltage Regulator
C3 helps in ripple rejection upto 15dB
D1 protect the device against input short circuit
D2 protect against output short circuit for capacitance discharging
C2 of 1 µF tantalum capacitor on the output helps to improve transient response
Useful Notes
3V to 40V DC
Vref = 1.25V
3.3V, 500mA

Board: 4 copper layers, 156 parts (0 on the bottom side), 103 nets, no tracks yet.
